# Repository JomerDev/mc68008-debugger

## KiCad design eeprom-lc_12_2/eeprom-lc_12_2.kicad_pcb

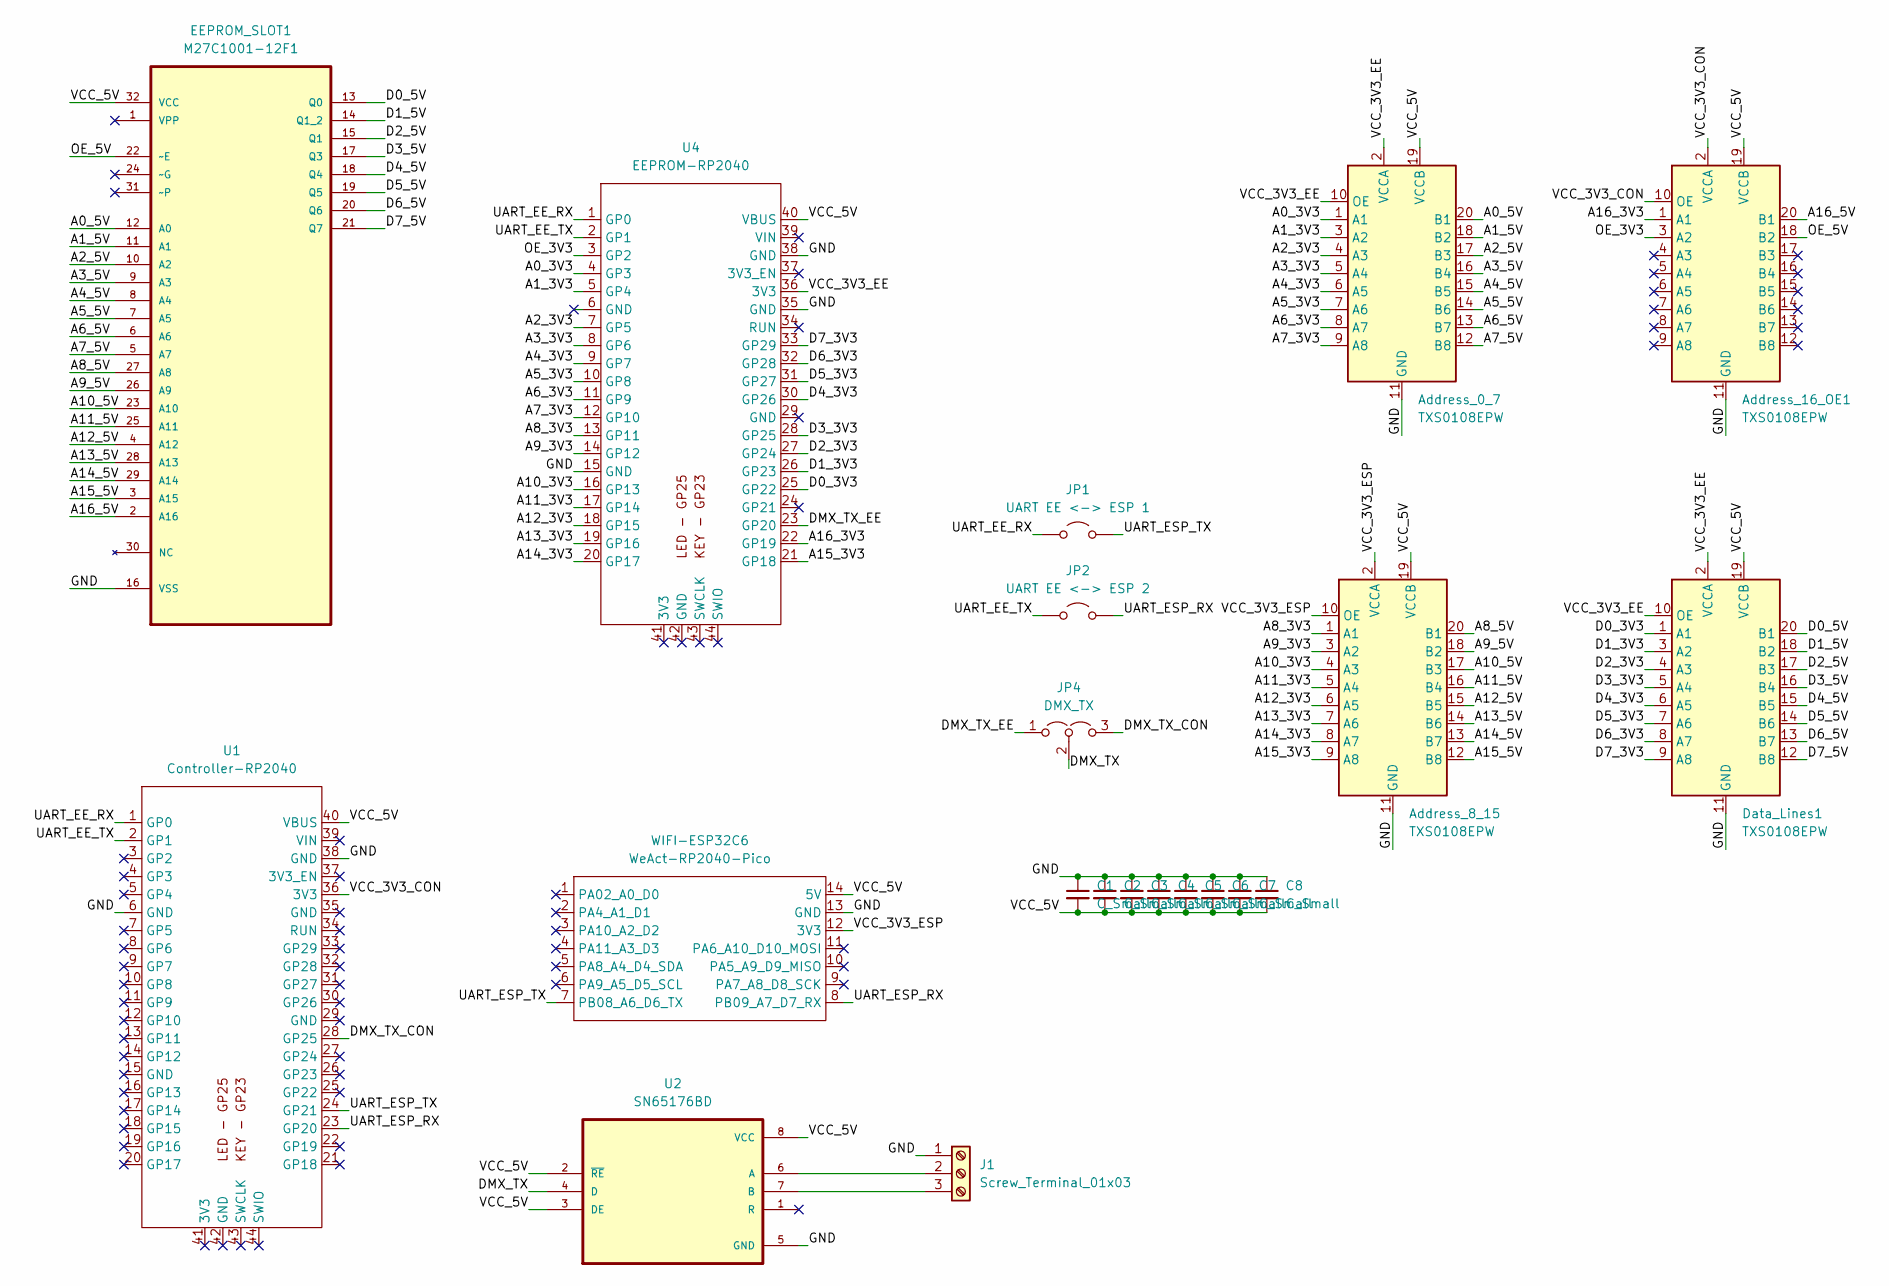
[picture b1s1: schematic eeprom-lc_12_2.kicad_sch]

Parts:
Address_0_7, Address_8_15, Address_16_OE1: TXS0108EPW; TSSOP-20_4.4x6.5mm_P0.65mm
C1, C2, C3, C4, C5, C6, C7, C8: C_Small; C_0603_1608Metric_Pad1.08x0.95mm_HandSolder
Data_Lines1: TXS0108EPW; TSSOP-20_4.4x6.5mm_P0.65mm
EEPROM_SLOT1: M27C1001-12F1; DIP254P1524X572-32; MPN M27C1001-12F1
J1: Screw_Terminal_01x03; PinHeader_1x03_P2.54mm_Vertical
JP1: UART EE <-> ESP 1; TestPoint_2Pads_Pitch2.54mm_Drill0.8mm
JP2: UART EE <-> ESP 2; TestPoint_2Pads_Pitch2.54mm_Drill0.8mm
JP4: DMX_TX; PinHeader_1x03_P2.54mm_Horizontal
U1: Controller-RP2040; WeAct-RP2040-Pico
U2: SN65176BD; SOIC127P599X175-8N
U4: EEPROM-RP2040; WeAct-RP2040-Pico
WIFI-ESP32C6: WeAct-RP2040-Pico; MOUDLE14P-SMD-2.54-21X17.8MM

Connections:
/A0_3V3: Address_0_7.1 (A1), U4.4 (GP3)
/A0_5V: Address_0_7.20 (B1), EEPROM_SLOT1.12 (A0)
/A1_3V3: Address_0_7.3 (A2), U4.5 (GP4)
/A1_5V: Address_0_7.18 (B2), EEPROM_SLOT1.11 (A1)
/A2_3V3: Address_0_7.4 (A3), U4.7 (GP5)
/A2_5V: Address_0_7.17 (B3), EEPROM_SLOT1.10 (A2)
/A3_3V3: Address_0_7.5 (A4), U4.8 (GP6)
/A3_5V: Address_0_7.16 (B4), EEPROM_SLOT1.9 (A3)
/A4_3V3: Address_0_7.6 (A5), U4.9 (GP7)
/A4_5V: Address_0_7.15 (B5), EEPROM_SLOT1.8 (A4)
/A5_3V3: Address_0_7.7 (A6), U4.10 (GP8)
/A5_5V: Address_0_7.14 (B6), EEPROM_SLOT1.7 (A5)
/A6_3V3: Address_0_7.8 (A7), U4.11 (GP9)
/A6_5V: Address_0_7.13 (B7), EEPROM_SLOT1.6 (A6)
/A7_3V3: Address_0_7.9 (A8), U4.12 (GP10)
/A7_5V: Address_0_7.12 (B8), EEPROM_SLOT1.5 (A7)
/A8_3V3: Address_8_15.1 (A1), U4.13 (GP11)
/A8_5V: Address_8_15.20 (B1), EEPROM_SLOT1.27 (A8)
/A9_3V3: Address_8_15.3 (A2), U4.14 (GP12)
/A9_5V: Address_8_15.18 (B2), EEPROM_SLOT1.26 (A9)
/A10_3V3: Address_8_15.4 (A3), U4.16 (GP13)
/A10_5V: Address_8_15.17 (B3), EEPROM_SLOT1.23 (A10)
/A11_3V3: Address_8_15.5 (A4), U4.17 (GP14)
/A11_5V: Address_8_15.16 (B4), EEPROM_SLOT1.25 (A11)
/A12_3V3: Address_8_15.6 (A5), U4.18 (GP15)
/A12_5V: Address_8_15.15 (B5), EEPROM_SLOT1.4 (A12)
/A13_3V3: Address_8_15.7 (A6), U4.19 (GP16)
/A13_5V: Address_8_15.14 (B6), EEPROM_SLOT1.28 (A13)
/A14_3V3: Address_8_15.8 (A7), U4.20 (GP17)
/A14_5V: Address_8_15.13 (B7), EEPROM_SLOT1.29 (A14)
/A15_3V3: Address_8_15.9 (A8), U4.21 (GP18)
/A15_5V: Address_8_15.12 (B8), EEPROM_SLOT1.3 (A15)
/A16_3V3: Address_16_OE1.1 (A1), U4.22 (GP19)
/A16_5V: Address_16_OE1.20 (B1), EEPROM_SLOT1.2 (A16)
/D0_3V3: Data_Lines1.1 (A1), U4.25 (GP22)
/D0_5V: Data_Lines1.20 (B1), EEPROM_SLOT1.13 (Q0)
/D1_3V3: Data_Lines1.3 (A2), U4.26 (GP23)
/D1_5V: Data_Lines1.18 (B2), EEPROM_SLOT1.14 (Q1_2)
/D2_3V3: Data_Lines1.4 (A3), U4.27 (GP24)
/D2_5V: Data_Lines1.17 (B3), EEPROM_SLOT1.15 (Q1)
/D3_3V3: Data_Lines1.5 (A4), U4.28 (GP25)
/D3_5V: Data_Lines1.16 (B4), EEPROM_SLOT1.17 (Q3)
/D4_3V3: Data_Lines1.6 (A5), U4.30 (GP26)
/D4_5V: Data_Lines1.15 (B5), EEPROM_SLOT1.18 (Q4)
/D5_3V3: Data_Lines1.7 (A6), U4.31 (GP27)
/D5_5V: Data_Lines1.14 (B6), EEPROM_SLOT1.19 (Q5)
/D6_3V3: Data_Lines1.8 (A7), U4.32 (GP28)
/D6_5V: Data_Lines1.13 (B7), EEPROM_SLOT1.20 (Q6)
/D7_3V3: Data_Lines1.9 (A8), U4.33 (GP29)
/D7_5V: Data_Lines1.12 (B8), EEPROM_SLOT1.21 (Q7)
/DMX_TX: JP4.2 (C), U2.4 (D); also elsewhere on the board
/DMX_TX_CON: JP4.3 (B), U1.28 (GP25)
/DMX_TX_EE: JP4.1 (A), U4.23 (GP20)
/GND: Address_0_7.11 (GND), Address_8_15.11 (GND), Address_16_OE1.11 (GND), C1.1, C2.1, C3.1, C4.1, C5.1, C6.1, C7.1, C8.1, Data_Lines1.11 (GND), EEPROM_SLOT1.16 (VSS), J1.1, U1.6 (GND), U1.38 (GND), U2.5 (GND), U4.15 (GND), U4.35 (GND), U4.38 (GND), WIFI-ESP32C6.13 (GND); also elsewhere on the board
/OE_3V3: Address_16_OE1.3 (A2), U4.3 (GP2)
/OE_5V: Address_16_OE1.18 (B2), EEPROM_SLOT1.22 (~E)
/UART_EE_RX: JP1.1 (A), U1.1 (GP0), U4.1 (GP0)
/UART_EE_TX: JP2.1 (A), U1.2 (GP1), U4.2 (GP1)
/UART_ESP_RX: JP2.2 (B), U1.23 (GP20), WIFI-ESP32C6.8 (PB09_A7_D7_RX)
/UART_ESP_TX: JP1.2 (B), U1.24 (GP21), WIFI-ESP32C6.7 (PB08_A6_D6_TX)
/VCC_3V3_CON: Address_16_OE1.2 (VCCA), Address_16_OE1.10 (OE), U1.36 (3V3)
/VCC_3V3_EE: Address_0_7.2 (VCCA), Address_0_7.10 (OE), Data_Lines1.2 (VCCA), Data_Lines1.10 (OE), U4.36 (3V3)
/VCC_3V3_ESP: Address_8_15.2 (VCCA), Address_8_15.10 (OE), WIFI-ESP32C6.12 (3V3)
/VCC_5V: Address_0_7.19 (VCCB), Address_8_15.19 (VCCB), Address_16_OE1.19 (VCCB), C1.2, C2.2, C3.2, C4.2, C5.2, C6.2, C7.2, C8.2, Data_Lines1.19 (VCCB), EEPROM_SLOT1.32 (VCC), U1.40 (VBUS), U2.2 (~RE), U2.3 (DE), U2.8 (VCC), U4.40 (VBUS), WIFI-ESP32C6.14 (5V); also elsewhere on the board
unnamed 64: J1.2, U2.6 (A); also elsewhere on the board
unnamed 65: J1.3, U2.7 (B); also elsewhere on the board

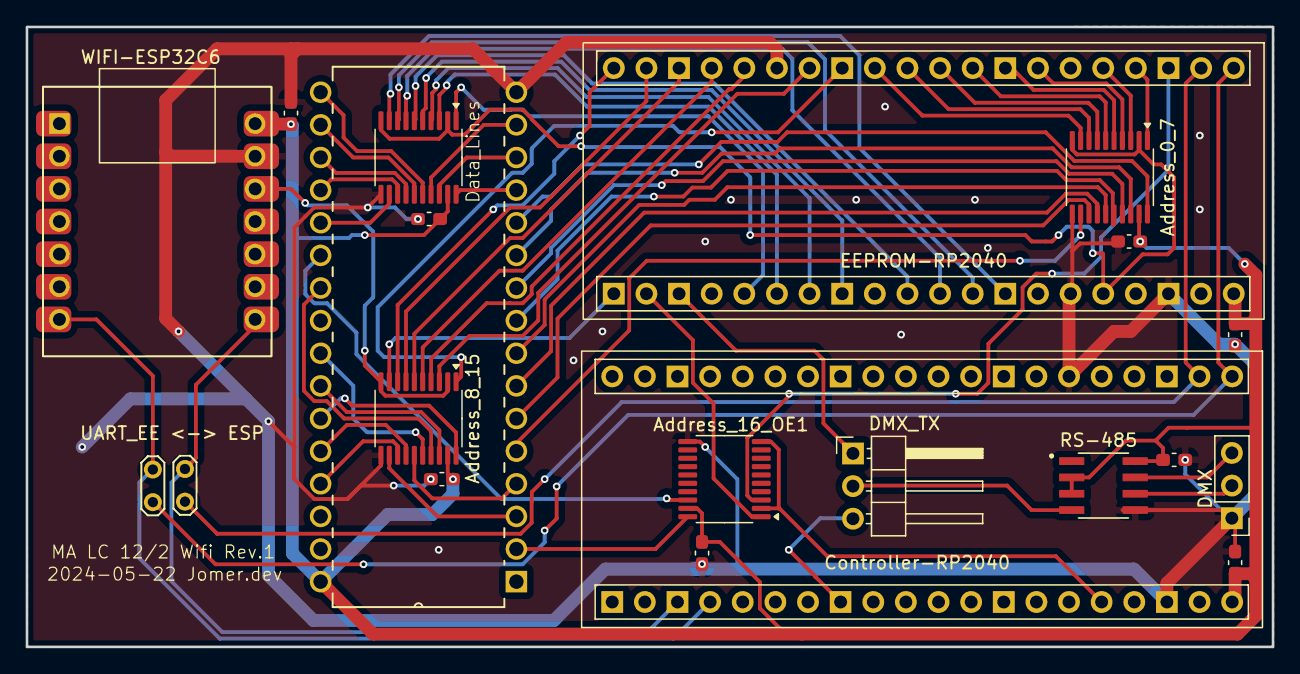
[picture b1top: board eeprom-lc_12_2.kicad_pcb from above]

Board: 2 copper layers, 97.0 x 48.3 mm, 21 parts (0 on the bottom side), 66 nets.

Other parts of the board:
RS-485: SN65176BD; SOIC127P599X175-8N

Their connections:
/DMX_TX: RS-485.4 (D); also elsewhere on the board
/GND: RS-485.5 (GND); also elsewhere on the board
/VCC_5V: RS-485.2 (~RE), RS-485.3 (DE), RS-485.8 (VCC); also elsewhere on the board
unnamed 64: RS-485.6 (A); also elsewhere on the board
unnamed 65: RS-485.7 (B); also elsewhere on the board

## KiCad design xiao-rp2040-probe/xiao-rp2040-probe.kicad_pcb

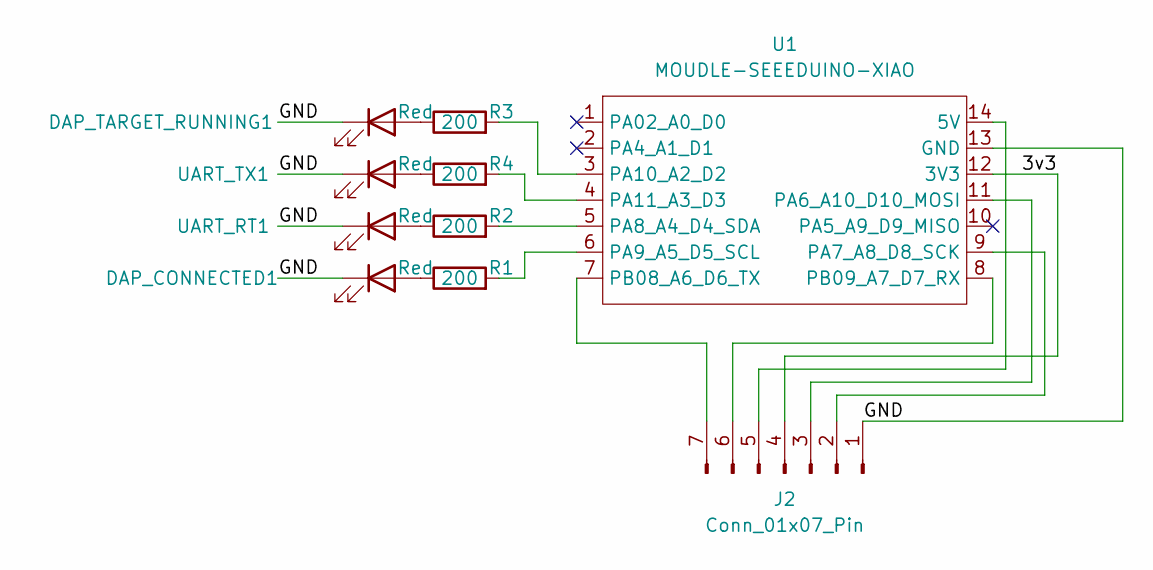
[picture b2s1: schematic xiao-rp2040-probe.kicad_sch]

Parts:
DAP_CONNECTED1: Red; LED_0603_1608Metric
DAP_TARGET_RUNNING1: Red; LED_0603_1608Metric
J2: Conn_01x07_Pin; PinHeader_1x07_P2.54mm_Horizontal
R1, R2, R3, R4: 200; R_0603_1608Metric
U1: MOUDLE-SEEEDUINO-XIAO; MOUDLE14P-SMD-2.54-21X17.8MM
UART_RT1: Red; LED_0603_1608Metric
UART_TX1: Red; LED_0603_1608Metric

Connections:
/3v3: J2.4, U1.12 (3V3)
/GND: DAP_CONNECTED1.1 (K), DAP_TARGET_RUNNING1.1 (K), J2.1, U1.13 (GND), UART_RT1.1 (K), UART_TX1.1 (K)
unnamed: DAP_CONNECTED1.2 (A), R1.1
unnamed: DAP_TARGET_RUNNING1.2 (A), R3.1
unnamed: J2.2, U1.9 (PA7_A8_D8_SCK)
unnamed: J2.3, U1.11 (PA6_A10_D10_MOSI)
unnamed: J2.5, U1.14 (5V)
unnamed: J2.6, U1.8 (PB09_A7_D7_RX)
unnamed: J2.7, U1.7 (PB08_A6_D6_TX)
unnamed: R2.2, U1.5 (PA8_A4_D4_SDA)
unnamed: R1.2, U1.6 (PA9_A5_D5_SCL)
unnamed: R3.2, U1.3 (PA10_A2_D2)
unnamed: R4.2, U1.4 (PA11_A3_D3)
unnamed: R2.1, UART_RT1.2 (A)
unnamed: R4.1, UART_TX1.2 (A)

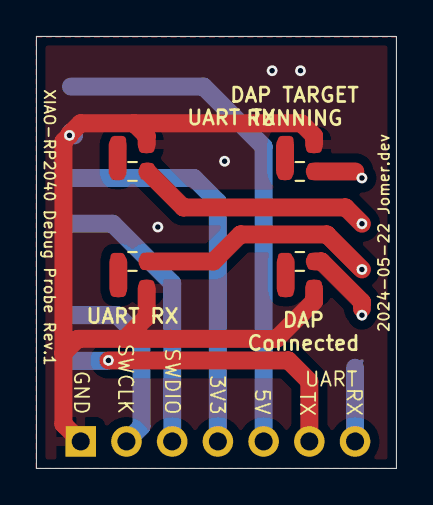
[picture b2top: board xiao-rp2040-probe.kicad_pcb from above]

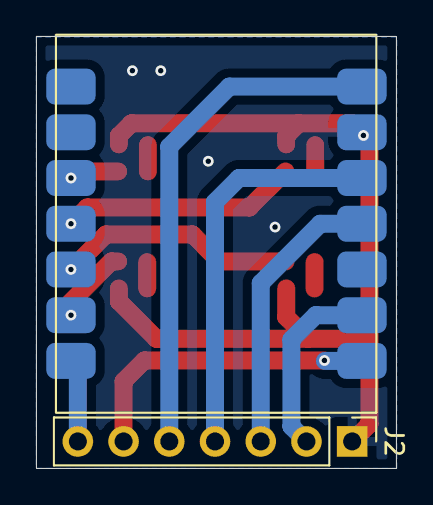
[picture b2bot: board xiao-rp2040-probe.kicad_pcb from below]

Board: 2 copper layers, 20.0 x 24.0 mm, 10 parts (2 on the bottom side), 15 nets.

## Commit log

2024-03-29 Some work on analyzer
2024-03-29 More work on analyzer and combiner
2024-03-29 Make button toggle
2024-03-30 Fix up analyzer pio
2024-03-31 Add clock, more work on combiner and analyzer
2024-03-31 Working analyzer and combiner
2024-04-13 Working on eeprom variant
2024-04-19 Add overclocking
2024-04-19 Add run from ram
2024-04-19 Trying to get run from ram to work
2024-04-20 Working run from RAM
2024-04-20 Try with cargo embed
2024-04-20 Split out into eeprom_test
2024-04-21 Latest changes
2024-04-25 More work reducing read errors
2024-04-27 Added two kicad projects
2024-05-01 Some work on eeprom code and pcb
2024-05-01 RGBW test
2024-05-03 Added wip server und web
2024-05-03 Figured out the needed libraries/features
2024-05-09 More work on pcb
2024-05-16 More pcb work
2024-05-18 FInishing up the pcb
2024-05-18 Fix wrong pinheaders
2024-05-18 Cleanup some traces
2024-05-22 Finished up the eeprom pcb
2024-05-23 Last pcb changes before order
